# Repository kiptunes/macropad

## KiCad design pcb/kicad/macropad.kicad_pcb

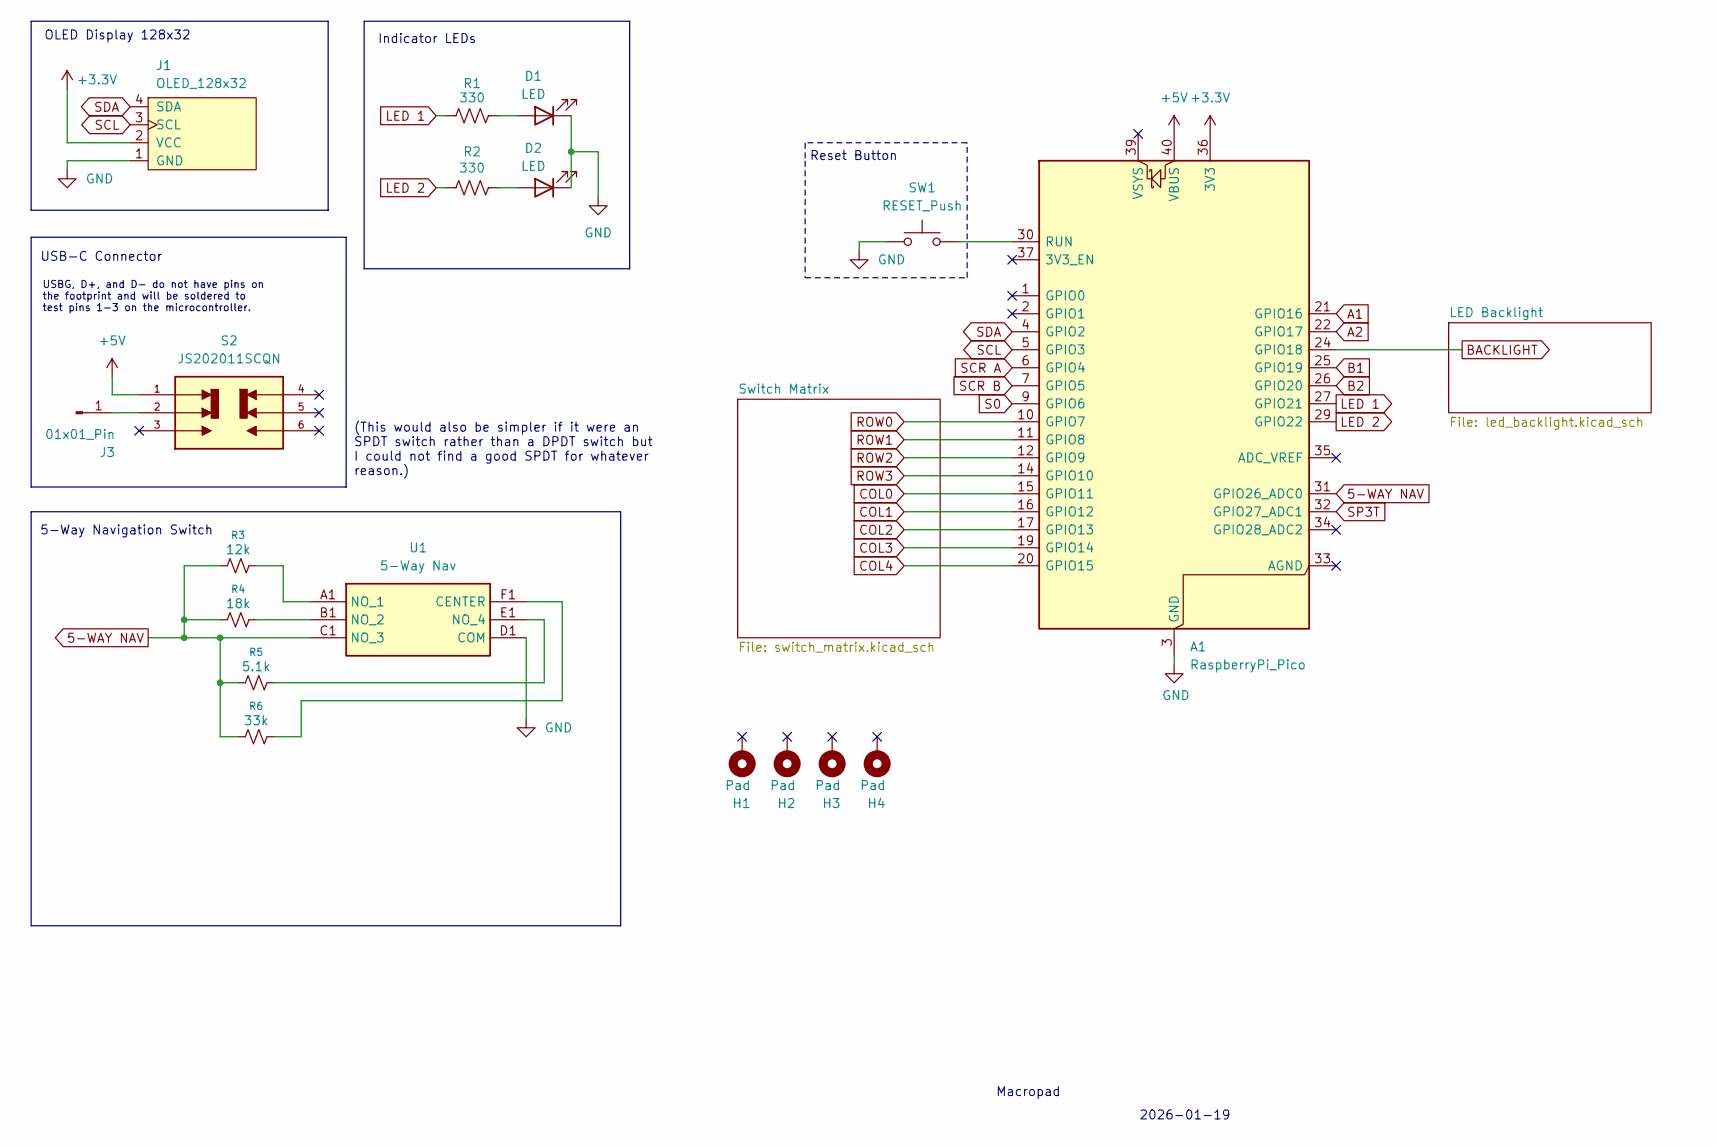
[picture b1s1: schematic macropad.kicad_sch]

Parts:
A1: RaspberryPi_Pico; RaspberryPi_Pico_Common_THT
D1, D2: LED; LED_D3.0mm
H1, H2, H3, H4: Pad; MountingHole_2.2mm_M2_Pad
J1: OLED_128x32; PinHeader_1x04_P2.54mm_Vertical
J3: 01x01_Pin; SolderWire-0.25sqmm_1x01_D0.65mm_OD2mm
R1, R2: 330; R_Axial_DIN0207_L6.3mm_D2.5mm_P10.16mm_Horizontal
R3: 12k; R_Axial_DIN0207_L6.3mm_D2.5mm_P10.16mm_Horizontal
R4: 18k; R_Axial_DIN0207_L6.3mm_D2.5mm_P10.16mm_Horizontal
R5: 5.1k; R_Axial_DIN0207_L6.3mm_D2.5mm_P10.16mm_Horizontal
R6: 33k; R_Axial_DIN0207_L6.3mm_D2.5mm_P10.16mm_Horizontal
S2: JS202011SCQN; SW_JS202011SCQN; PARTREV 26 May 22
SW1: RESET_Push; SW_Tactile_SPST_NO_Straight_CK_PTS636Sx25SMTRLFS
U1: 5-Way Nav; MUAS90R; Manufacturer_Part_Number MU-AS90R; Mouser Part Number 642-MU-AS90R

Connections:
5-WAY NAV: A1.31 (GPIO26_ADC0), R3.1, R4.1, R5.1, R6.1, U1.C1 (NO_3)
+3.3V: A1.36 (3V3), J1.2 (VCC)
+5V: A1.40 (VBUS), S2.1; also elsewhere on the board
A1: A1.21 (GPIO16); also elsewhere on the board
A2: A1.22 (GPIO17); also elsewhere on the board
B1: A1.25 (GPIO19); also elsewhere on the board
B2: A1.26 (GPIO20); also elsewhere on the board
BACKLIGHT: A1.24 (GPIO18); also elsewhere on the board
COL0: A1.15 (GPIO11); also elsewhere on the board
COL1: A1.16 (GPIO12); also elsewhere on the board
COL2: A1.17 (GPIO13); also elsewhere on the board
COL3: A1.19 (GPIO14); also elsewhere on the board
COL4: A1.20 (GPIO15); also elsewhere on the board
GND: A1.3 (GND), A1.8 (GND), A1.13 (GND), A1.18 (GND), A1.23 (GND), A1.28 (GND), A1.38 (GND), D1.1 (K), D2.1 (K), J1.1 (GND), SW1.1, U1.D1 (COM); also elsewhere on the board
LED 1: A1.27 (GPIO21), R1.1
LED 2: A1.29 (GPIO22), R2.1
unnamed: A1.30 (RUN), SW1.2
unnamed: D1.2 (A), R1.2
unnamed: D2.2 (A), R2.2
unnamed: J3.1, S2.2
unnamed: R6.2, U1.F1 (CENTER)
unnamed: R3.2, U1.A1 (NO_1)
unnamed: R4.2, U1.B1 (NO_2)
unnamed: R5.2, U1.E1 (NO_4)
ROW0: A1.10 (GPIO7); also elsewhere on the board
ROW1: A1.11 (GPIO8); also elsewhere on the board
ROW2: A1.12 (GPIO9); also elsewhere on the board
ROW3: A1.14 (GPIO10); also elsewhere on the board
S0: A1.9 (GPIO6); also elsewhere on the board
SCL: A1.5 (GPIO3), J1.3 (SCL)
SCR A: A1.6 (GPIO4); also elsewhere on the board
SCR B: A1.7 (GPIO5); also elsewhere on the board
SDA: A1.4 (GPIO2), J1.4 (SDA)
SP3T: A1.32 (GPIO27_ADC1); also elsewhere on the board

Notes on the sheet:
USBG, D+, and D- do not have pins on the footprint and will be soldered to test pins 1-3 on the microcontroller.
OLED Display 128x32
USB-C Connector
(This would also be simpler if it were an SPDT switch rather than a DPDT switch but I could not find a good SPDT for whatever reason.)
2026-01-19
Macropad
Reset Button
5-Way Navigation Switch
Indicator LEDs

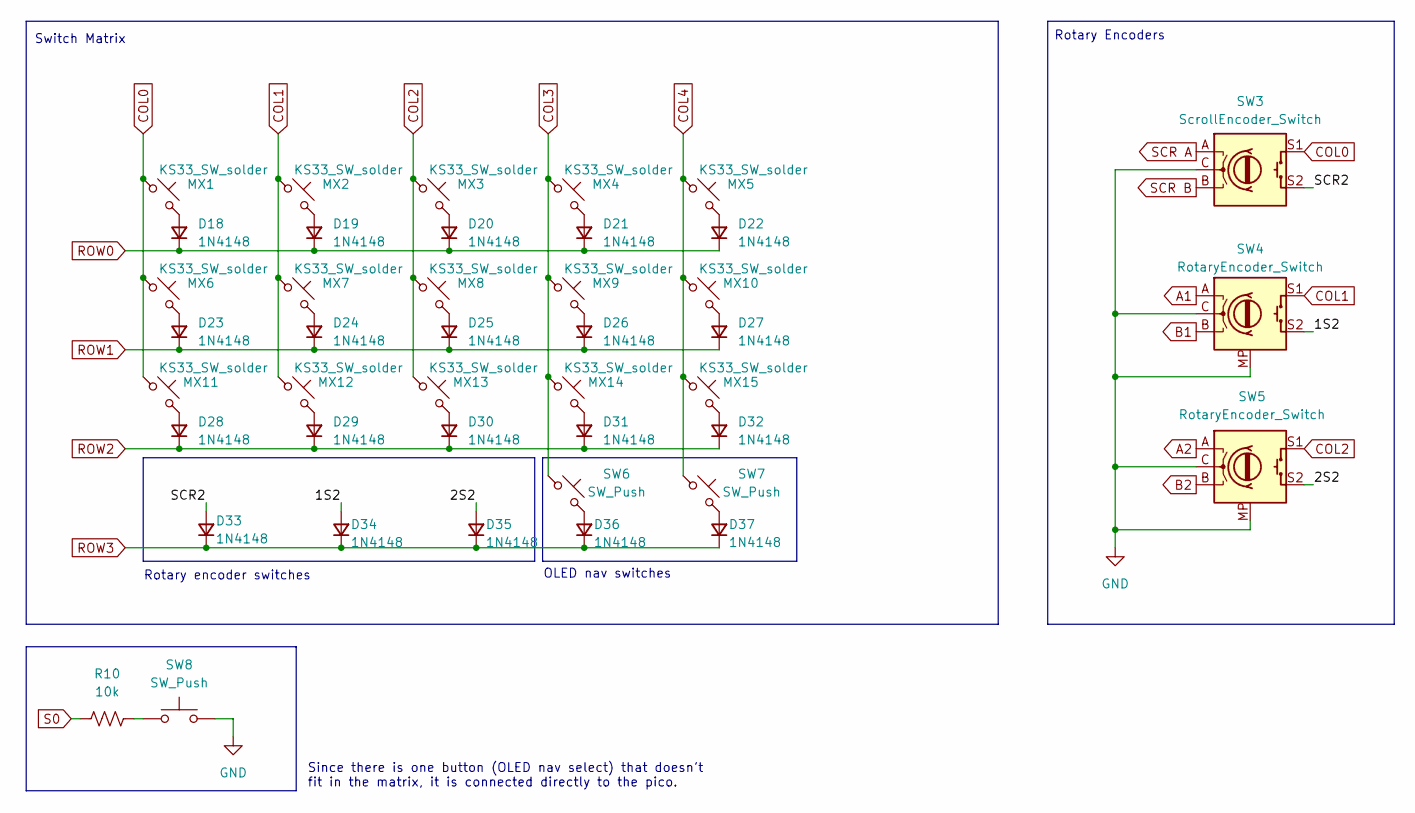
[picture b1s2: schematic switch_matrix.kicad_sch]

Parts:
D18, D19, D20, D21, D22, D23, D24, D25, D26, D27, D28, D29, D30, D31, D32, D33, D34, D35, D36, D37: 1N4148; Diode_DO-35; PARTREV 5
MX1, MX2, MX3, MX4, MX5, MX6, MX7, MX8, MX9, MX10, MX11, MX12, MX13, MX14, MX15: KS33_SW_solder; SW_KS33_1u
R10: 10k; R_Axial_DIN0207_L6.3mm_D2.5mm_P10.16mm_Horizontal
SW3: ScrollEncoder_Switch; CKW12
SW4, SW5: RotaryEncoder_Switch; RotaryEncoder_Alps_EC11E-Switch_Vertical_H20mm
SW6, SW7, SW8: SW_Push; SW_PUSH_6mm_H4.3mm

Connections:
/Switch Matrix/1S2: D34.2 (A), SW4.S2
/Switch Matrix/2S2: D35.2 (A), SW5.S2
/Switch Matrix/SCR2: D33.2 (A), SW3.S2
A1: SW4.A; also elsewhere on the board
A2: SW5.A; also elsewhere on the board
B1: SW4.B; also elsewhere on the board
B2: SW5.B; also elsewhere on the board
COL0: MX1.1, MX6.1, MX11.1, SW3.S1; also elsewhere on the board
COL1: MX2.1, MX7.1, MX12.1, SW4.S1; also elsewhere on the board
COL2: MX3.1, MX8.1, MX13.1, SW5.S1; also elsewhere on the board
COL3: MX4.1, MX9.1, MX14.1, SW6.1; also elsewhere on the board
COL4: MX5.1, MX10.1, MX15.1, SW7.1; also elsewhere on the board
GND: SW3.C, SW4.C, SW4.MP, SW5.C, SW5.MP, SW8.2; also elsewhere on the board
unnamed: D18.2 (A), MX1.2
unnamed: D19.2 (A), MX2.2
unnamed: D20.2 (A), MX3.2
unnamed: D21.2 (A), MX4.2
unnamed: D22.2 (A), MX5.2
unnamed: D23.2 (A), MX6.2
unnamed: D24.2 (A), MX7.2
unnamed: D25.2 (A), MX8.2
unnamed: D26.2 (A), MX9.2
unnamed: D27.2 (A), MX10.2
unnamed: D28.2 (A), MX11.2
unnamed: D29.2 (A), MX12.2
unnamed: D30.2 (A), MX13.2
unnamed: D31.2 (A), MX14.2
unnamed: D32.2 (A), MX15.2
unnamed: D36.2 (A), SW6.2
unnamed: D37.2 (A), SW7.2
unnamed: R10.2, SW8.1
ROW0: D18.1 (K), D19.1 (K), D20.1 (K), D21.1 (K), D22.1 (K); also elsewhere on the board
ROW1: D23.1 (K), D24.1 (K), D25.1 (K), D26.1 (K), D27.1 (K); also elsewhere on the board
ROW2: D28.1 (K), D29.1 (K), D30.1 (K), D31.1 (K), D32.1 (K); also elsewhere on the board
ROW3: D33.1 (K), D34.1 (K), D35.1 (K), D36.1 (K), D37.1 (K); also elsewhere on the board
S0: R10.1; also elsewhere on the board
SCR A: SW3.A; also elsewhere on the board
SCR B: SW3.B; also elsewhere on the board

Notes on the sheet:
Rotary encoder switches
OLED nav switches
Rotary Encoders
Since there is one button (OLED nav select) that doesn't fit in the matrix, it is connected directly to the pico.
Switch Matrix

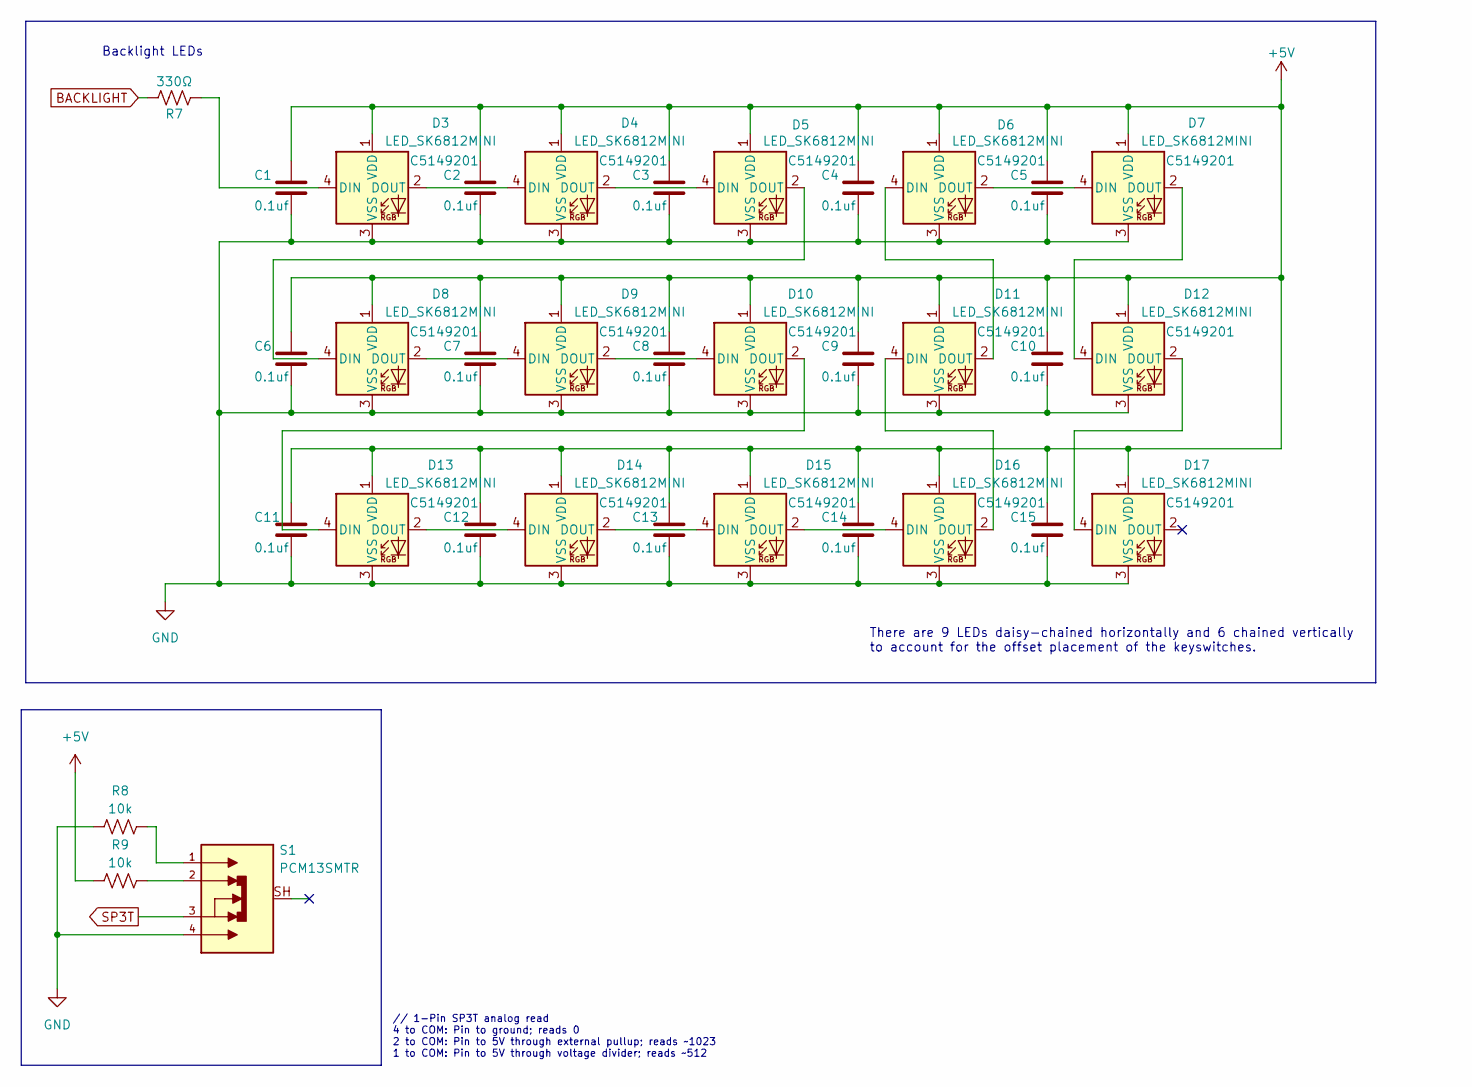
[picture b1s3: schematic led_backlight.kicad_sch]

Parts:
C1, C2, C3, C4, C5, C6, C7, C8, C9, C10, C11, C12, C13, C14, C15: 0.1uf; C_1206_3216Metric
D3, D4, D5, D6, D7, D8, D9, D10, D11, D12, D13, D14, D15, D16, D17: LED_SK6812MINI; LCSC C5149201
R7: 330Ω; R_Axial_DIN0207_L6.3mm_D2.5mm_P10.16mm_Horizontal
R8, R9: 10k; R_Axial_DIN0207_L6.3mm_D2.5mm_P10.16mm_Horizontal
S1: PCM13SMTR; SW_PCM13SMTR; PARTREV VL 03/14/25

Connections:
+5V: C1.1, C2.1, C3.1, C4.1, C5.1, C6.1, C7.1, C8.1, C9.1, C10.1, C11.1, C12.1, C13.1, C14.1, C15.1, D3.1 (VDD), D4.1 (VDD), D5.1 (VDD), D6.1 (VDD), D7.1 (VDD), D8.1 (VDD), D9.1 (VDD), D10.1 (VDD), D11.1 (VDD), D12.1 (VDD), D13.1 (VDD), D14.1 (VDD), D15.1 (VDD), D16.1 (VDD), D17.1 (VDD), R9.1; also elsewhere on the board
BACKLIGHT: R7.1; also elsewhere on the board
GND: C1.2, C2.2, C3.2, C4.2, C5.2, C6.2, C7.2, C8.2, C9.2, C10.2, C11.2, C12.2, C13.2, C14.2, C15.2, D3.3 (VSS), D4.3 (VSS), D5.3 (VSS), D6.3 (VSS), D7.3 (VSS), D8.3 (VSS), D9.3 (VSS), D10.3 (VSS), D11.3 (VSS), D12.3 (VSS), D13.3 (VSS), D14.3 (VSS), D15.3 (VSS), D16.3 (VSS), D17.3 (VSS), R8.1, S1.4; also elsewhere on the board
unnamed: D3.4 (DIN), R7.2
unnamed: D3.2 (DOUT), D4.4 (DIN)
unnamed: D4.2 (DOUT), D5.4 (DIN)
unnamed: D5.2 (DOUT), D8.4 (DIN)
unnamed: D6.2 (DOUT), D7.4 (DIN)
unnamed: D8.2 (DOUT), D9.4 (DIN)
unnamed: D9.2 (DOUT), D10.4 (DIN)
unnamed: D10.2 (DOUT), D13.4 (DIN)
unnamed: D11.4 (DIN), D16.2 (DOUT)
unnamed: D6.4 (DIN), D11.2 (DOUT)
unnamed: D7.2 (DOUT), D12.4 (DIN)
unnamed: D12.2 (DOUT), D17.4 (DIN)
unnamed: D13.2 (DOUT), D14.4 (DIN)
unnamed: D14.2 (DOUT), D15.4 (DIN)
unnamed: D15.2 (DOUT), D16.4 (DIN)
unnamed: R8.2, S1.1
unnamed: R9.2, S1.2
SP3T: S1.3; also elsewhere on the board

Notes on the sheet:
There are 9 LEDs daisy-chained horizontally and 6 chained vertically to account for the offset placement of the keyswitches.
Backlight LEDs
// 1-Pin SP3T analog read 4 to COM: Pin to ground; reads 0 2 to COM: Pin to 5V through external pullup; reads ~1023 1 to COM: Pin to 5V through voltage divider; reads ~512

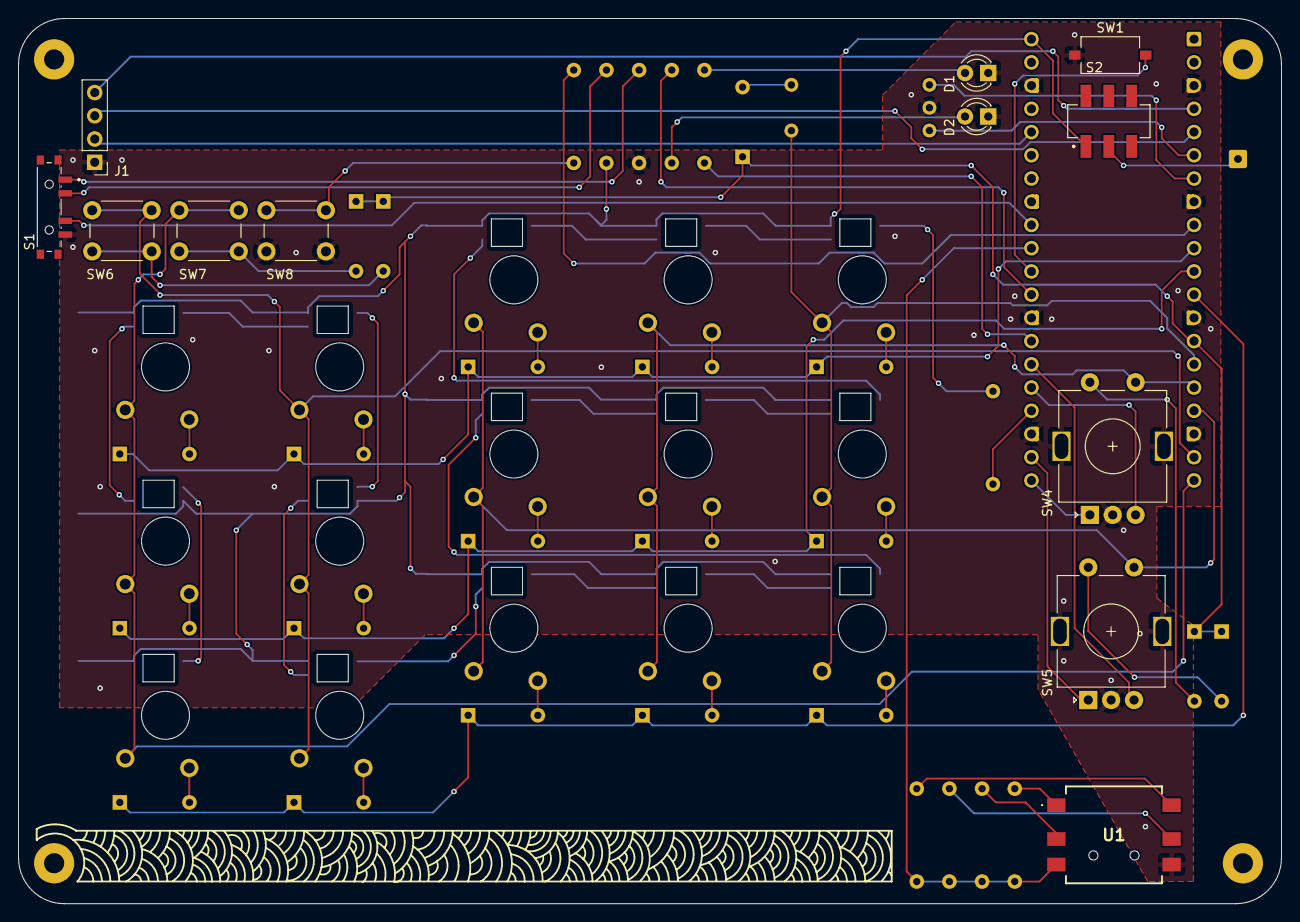
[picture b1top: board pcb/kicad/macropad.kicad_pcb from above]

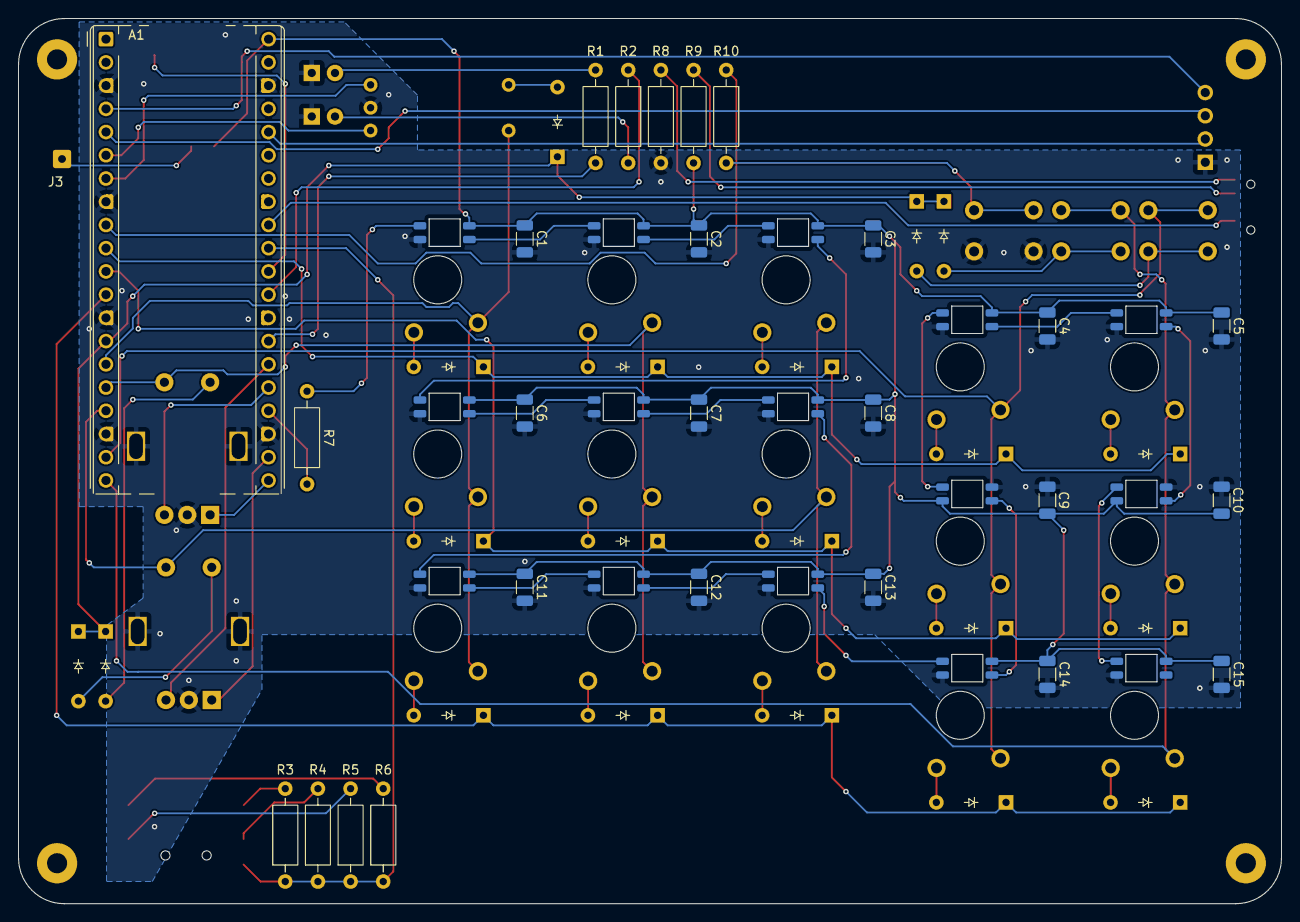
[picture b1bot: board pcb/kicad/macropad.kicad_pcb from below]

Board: 2 copper layers, 138.1 x 96.8 mm, 94 parts (66 on the bottom side), 72 nets.

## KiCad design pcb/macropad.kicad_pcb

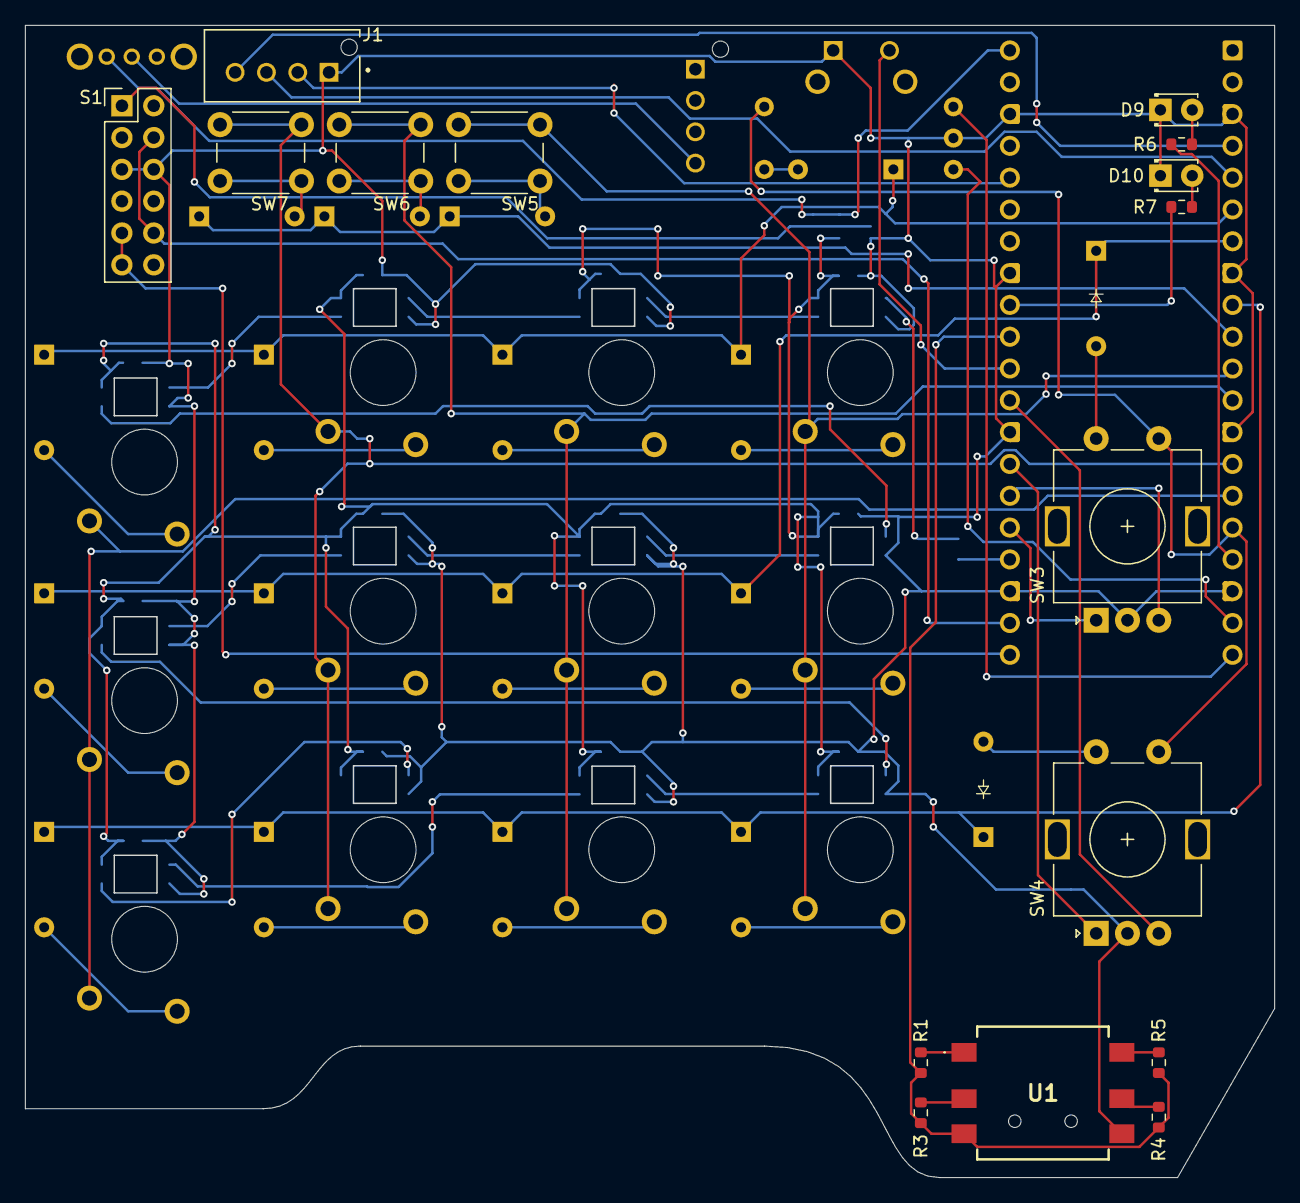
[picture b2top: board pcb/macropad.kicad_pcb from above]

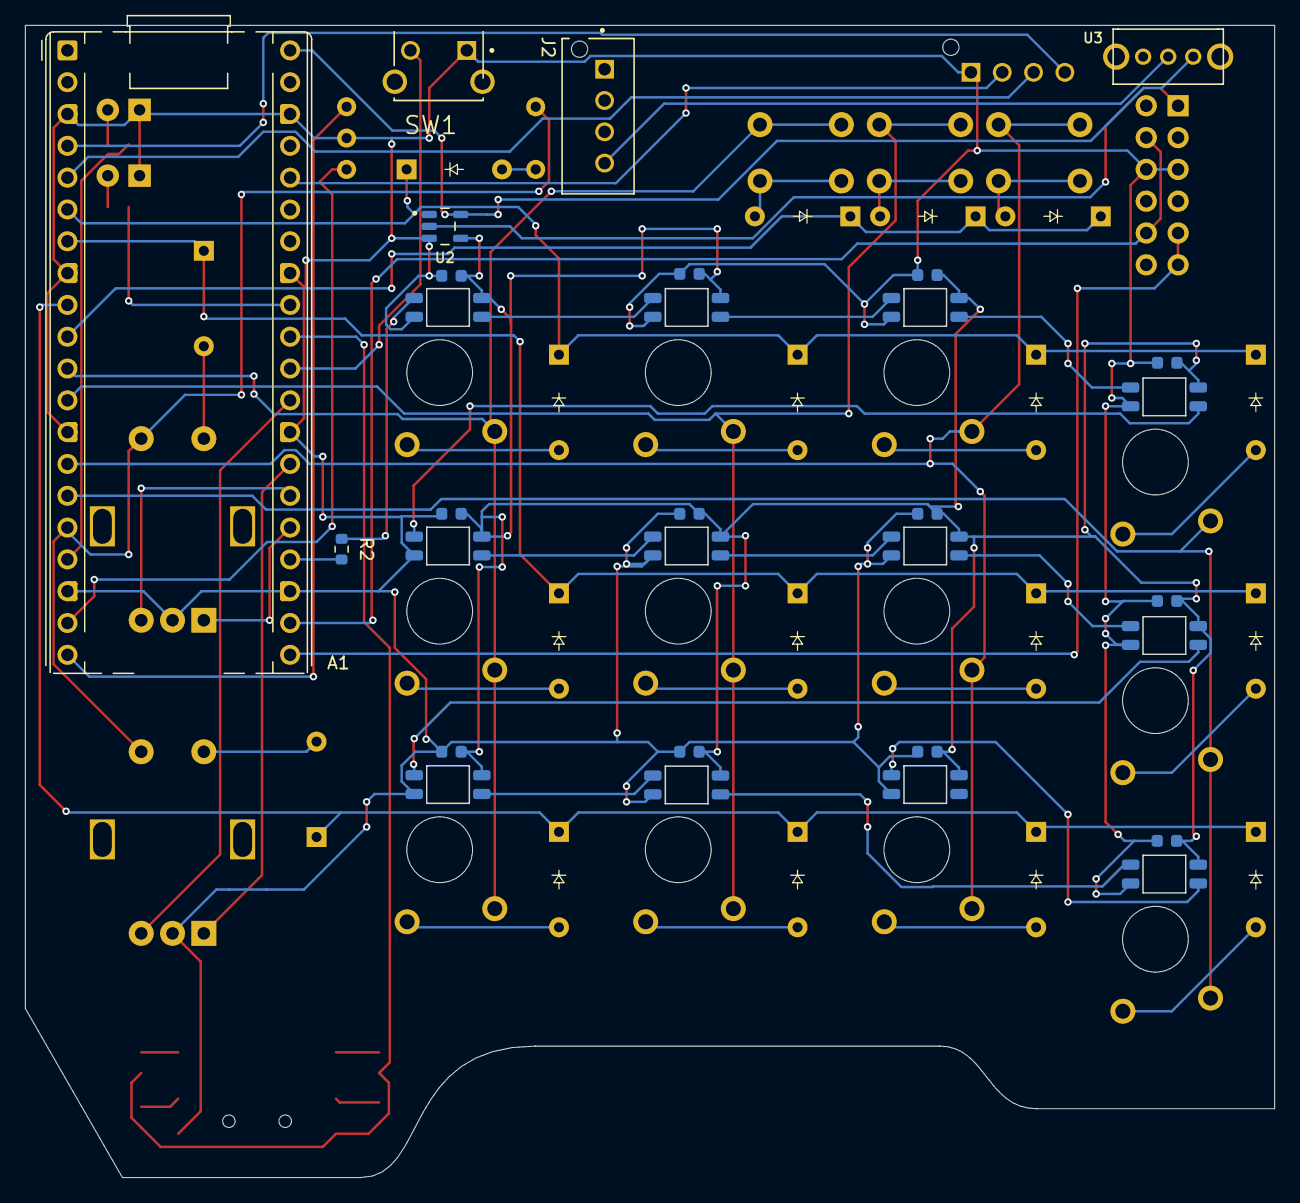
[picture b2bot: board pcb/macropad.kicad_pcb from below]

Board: 2 copper layers, 99.8 x 92.0 mm, 77 parts (46 on the bottom side), 66 nets.

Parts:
A1: RaspberryPi_Pico; RaspberryPi_Pico_Common_THT
C1, C2, C3, C4, C5, C6, C7, C8, C9, C10, C11, C12: 0.1uf; Capacitor_0603
D1, D2, D3, D4, D5, D6, D7, D8, D11, D12, D13, D14: LED_SK6812MINI
D9, D10: LED; LED_D1.8mm_W3.3mm_H2.4mm
D15, D16, D17, D18, D20, D21, D22, D23, D25, D26, D27, D28, D30, D31, D32: 1N4148; Diode_DO-35
D19, D24, D29: 1N4148W; Diode_DO-35
J1: OLED_128x32; JST_B4B-XH-AM__LF__SN_
J2: 4P4C; JST_B4B-XH-AM__LF__SN_
MX1, MX2, MX3, MX4, MX5, MX6, MX7, MX8, MX9, MX10, MX11, MX12: KS33_SW_solder; SW_KS33_1u
R1: 12k; R_0603_1608Metric
R2, R6: 330Ω; R_0603_1608Metric
R3: 18k; R_0603_1608Metric
R4: 5.1k; R_0603_1608Metric
R5: 33k; R_0603_1608Metric
R7: 330; R_0603_1608Metric
S1: DP4T Slide Switch; PinHeader_2x06_P2.54mm_Vertical
SW1: RESET_Push; SW_TL1105VF160Q
SW2: RotaryEncoder_Switch; CKW12
SW3, SW4: RotaryEncoder_Switch; RotaryEncoder_Alps_EC11E-Switch_Vertical_H20mm
SW5, SW6, SW7: Soft_Push; SW_PUSH_6mm
U1: 5-Way Nav; MUAS90R
U2: NOT Gate; SOT95P280X145-5N
U3: ON/OFF; SK12D07VG4

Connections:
5-WAY NAV: A1.31 (GPIO26_ADC0), R1.1, R3.1, R4.1, R5.1, U1.C1 (NO_3)
+3.3V: A1.36 (3V3), J1.2 (VCC)
+5V: A1.40 (VBUS), U2.5 (VCC), U3.1
A1: A1.25 (GPIO19), SW3.A
A2: A1.27 (GPIO21), SW4.A
B1: A1.26 (GPIO20), SW3.B
B2: A1.29 (GPIO22), SW4.B
BACKLIGHT: A1.24 (GPIO18), R2.1
BUTTONS: A1.10 (GPIO7), D30.1 (K), D31.1 (K), D32.1 (K)
COL0: A1.11 (GPIO8), MX1.1, MX5.1, MX9.1, SW5.1
COL1: A1.12 (GPIO9), MX2.1, MX6.1, MX10.1, SW6.1
COL2: A1.14 (GPIO10), MX3.1, MX7.1, MX11.1, SW7.1
COL3: A1.15 (GPIO11), MX4.1, MX8.1, MX12.1
DP4T 1: A1.21 (GPIO16), S1.4, S1.5
DP4T 2: A1.22 (GPIO17), S1.7, S1.9
ENC SW: A1.16 (GPIO12), SW2.1, SW3.S1, SW4.S1
GND: A1.3 (GND), A1.8 (GND), A1.13 (GND), A1.18 (GND), A1.23 (GND), A1.28 (GND), A1.33 (AGND), A1.38 (GND), C1.2, C2.2, C3.2, C4.2, C5.2, C6.2, C7.2, C8.2, C9.2, C10.2, C11.2, C12.2, D1.3 (VSS), D2.3 (VSS), D3.3 (VSS), D4.3 (VSS), D5.3 (VSS), D6.3 (VSS), D7.3 (VSS), D8.3 (VSS), D9.1 (K), D10.1 (K), D11.3 (VSS), D12.3 (VSS), D13.3 (VSS), D14.3 (VSS), J1.1 (GND), S1.3, S1.8, SW1.1, SW2.C, SW3.C, SW4.C, U1.D1 (COM), U2.3 (GND)
LED 1: A1.17 (GPIO13), R6.1
LED 2: A1.32 (GPIO27_ADC1), R7.1
unnamed: A1.30 (RUN), SW1.2
unnamed: D1.4 (DIN), R2.2
unnamed: D1.2 (DOUT), D2.4 (DIN)
unnamed: C1.1, C2.1, C3.1, C4.1, C5.1, C6.1, C7.1, C8.1, C9.1, C10.1, C11.1, C12.1, D1.1 (VDD), D2.1 (VDD), D3.1 (VDD), D4.1 (VDD), D5.1 (VDD), D6.1 (VDD), D7.1 (VDD), D8.1 (VDD), D11.1 (VDD), D12.1 (VDD), D13.1 (VDD), D14.1 (VDD), U2.4 (Y)
unnamed: D2.2 (DOUT), D3.4 (DIN)
unnamed: D3.2 (DOUT), D4.4 (DIN)
unnamed: D4.2 (DOUT), D5.4 (DIN)
unnamed: D5.2 (DOUT), D6.4 (DIN)
unnamed: D6.2 (DOUT), D7.4 (DIN)
unnamed: D7.2 (DOUT), D8.4 (DIN)
unnamed: D9.2 (A), R6.2
unnamed: D10.2 (A), R7.2
unnamed: D8.2 (DOUT), D11.4 (DIN)
unnamed: D11.2 (DOUT), D12.4 (DIN)
unnamed: D12.2 (DOUT), D13.4 (DIN)
unnamed: D13.2 (DOUT), D14.4 (DIN)
unnamed: D15.2 (A), MX1.2
unnamed: D16.2 (A), MX2.2
unnamed: D17.2 (A), MX3.2
unnamed: D18.2 (A), MX4.2
unnamed: D19.2 (A), SW2.2
unnamed: D20.2 (A), MX5.2
unnamed: D21.2 (A), MX6.2
unnamed: D22.2 (A), MX7.2
unnamed: D23.2 (A), MX8.2
unnamed: D24.2 (A), SW3.S2
unnamed: D25.2 (A), MX9.2
unnamed: D26.2 (A), MX10.2
unnamed: D27.2 (A), MX11.2
unnamed: D28.2 (A), MX12.2
unnamed: D29.2 (A), SW4.S2
unnamed: D30.2 (A), SW5.2
unnamed: D31.2 (A), SW6.2
unnamed: D32.2 (A), SW7.2
unnamed: J2.4 (V), U3.COM
unnamed: R5.2, U1.F1 (CENTER)
unnamed: R1.2, U1.A1 (NO_1)
unnamed: R3.2, U1.B1 (NO_2)
unnamed: R4.2, U1.E1 (NO_4)
unnamed: S1.1, U2.2 (A)
ROW0: A1.6 (GPIO4), D15.1 (K), D16.1 (K), D17.1 (K), D18.1 (K), D19.1 (K)
ROW1: A1.7 (GPIO5), D20.1 (K), D21.1 (K), D22.1 (K), D23.1 (K), D24.1 (K)
ROW2: A1.9 (GPIO6), D25.1 (K), D26.1 (K), D27.1 (K), D28.1 (K), D29.1 (K)
SCL: A1.5 (GPIO3), J1.3 (SCL)
SCR A: A1.19 (GPIO14), SW2.A
SCR B: A1.20 (GPIO15), SW2.B
SDA: A1.4 (GPIO2), J1.4 (SDA)

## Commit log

2026-01-21 Rename pcb/macropad.kicad_pcb to pcb/kicad/macropad.kicad_pcb
2026-01-21 Rename pcb/macropad.kicad_prl to pcb/kicad/macropad.kicad_prl
2026-01-21 Rename pcb/macropad.kicad_pro to pcb/kicad/macropad.kicad_pro
2026-01-21 Rename pcb/macropad.kicad_sch to pcb/kicad/macropad.kicad_sch
2026-01-21 Create symbol
2026-01-21 Create f
2026-01-23 Routed PCB
2026-02-14 Added local footprints
2026-02-14 Added local symbols
2026-02-14 v2 schematic
2026-02-18 Added SP3T slide switch and removed unused libraries
2026-02-18 Routed PCB v2
2026-02-21 rsync qmk keyboard directory
2026-02-21 3d model for case and plate added
2026-02-21 updated 3d model files
2026-02-26 Removed old model
2026-02-26 Moved kicad libraries, culled unused
2026-02-26 Simplified pcb; now fits within 10x10cm
